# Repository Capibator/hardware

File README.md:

# V1.0 -> First tentative version with following features: 
made with Kicad, 2 layers, lots of vias :D 
- battery monitoring
- battery charge/discharge maintanance LIPO 
- buck boost regulator TPS 
- Source selector that can select between mcu_bat or +12V automatically
- An RTC that can keep time even without battery. helpful for critical memory and notifications. 
- An optional IO expander (PCF) providing 8 extra GPIO. can be left unpopulated. pcb should work fine. 
- MCU used is ESP32 with bluetooth and wifi hopefully both being utillized
- Heater and egg turner both AC, egg turner is the continous type and is the only type currently supported. 
- Main Voltage being used is +12V provided by jack, that will power fans, logic board. incase of power outage heavy stuff will be turned off automatically and it will go into power saving mode. 
- Outputs (All 12V)
    - Fan Exhaust 
    - Fan Continous 
    - Mist Maker 
    - LED lights 
    - Buzzer
    - Water Pump 
- Sensors/Inputs
    - Water level sensor
    - Display (I2C)
    - Rotary encoder for menu (left, right and click)
    - Temperature sensor (1 wire or digital)
    - Temperature sensor #2 (1 wire or digital)
- Indicators
    - Fault led, will light up if something is wrong according to code
    - Busy led, will turn on when turning eggs or saving to memory 
    - Con led, shows connectivity of wifi, if connected will light up
    - IO led, custom function or initial testing. 
    - Main power indicator led that will light up when 12V is connected through barrel jack. 

This is how it looks as of right now. 

PCB 

# Version 2 
Better placement, hopefully this is better. 
AC in one end and sensitive logic on the other. 

size 101.5mm x 61.4mm

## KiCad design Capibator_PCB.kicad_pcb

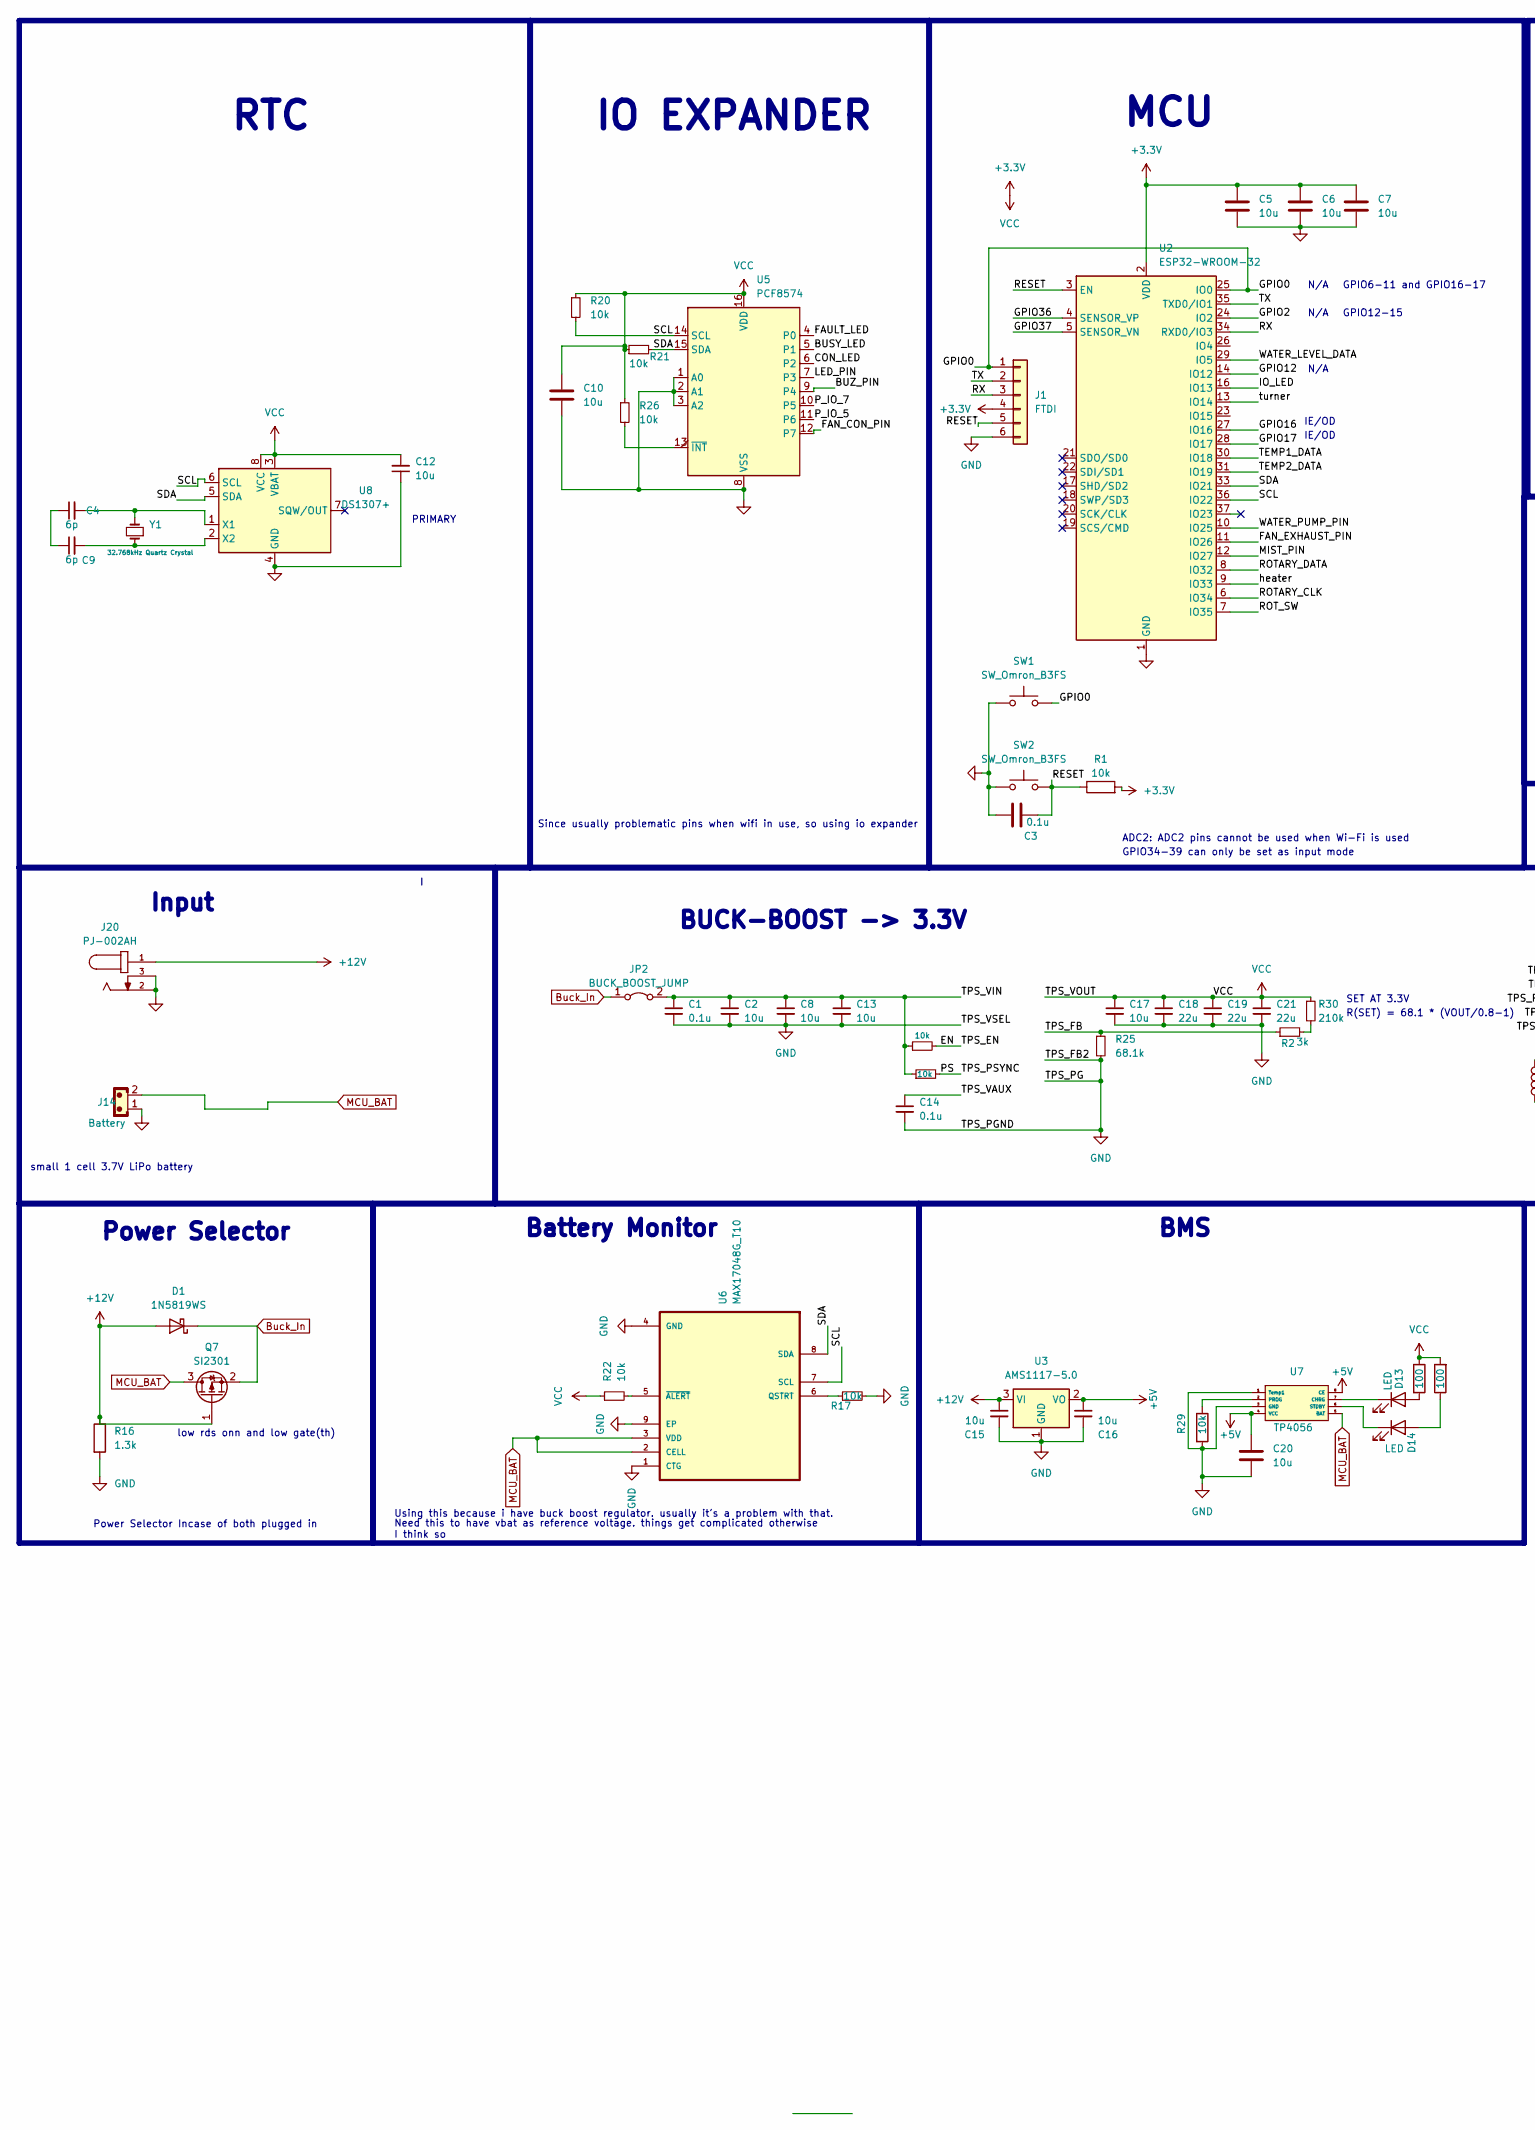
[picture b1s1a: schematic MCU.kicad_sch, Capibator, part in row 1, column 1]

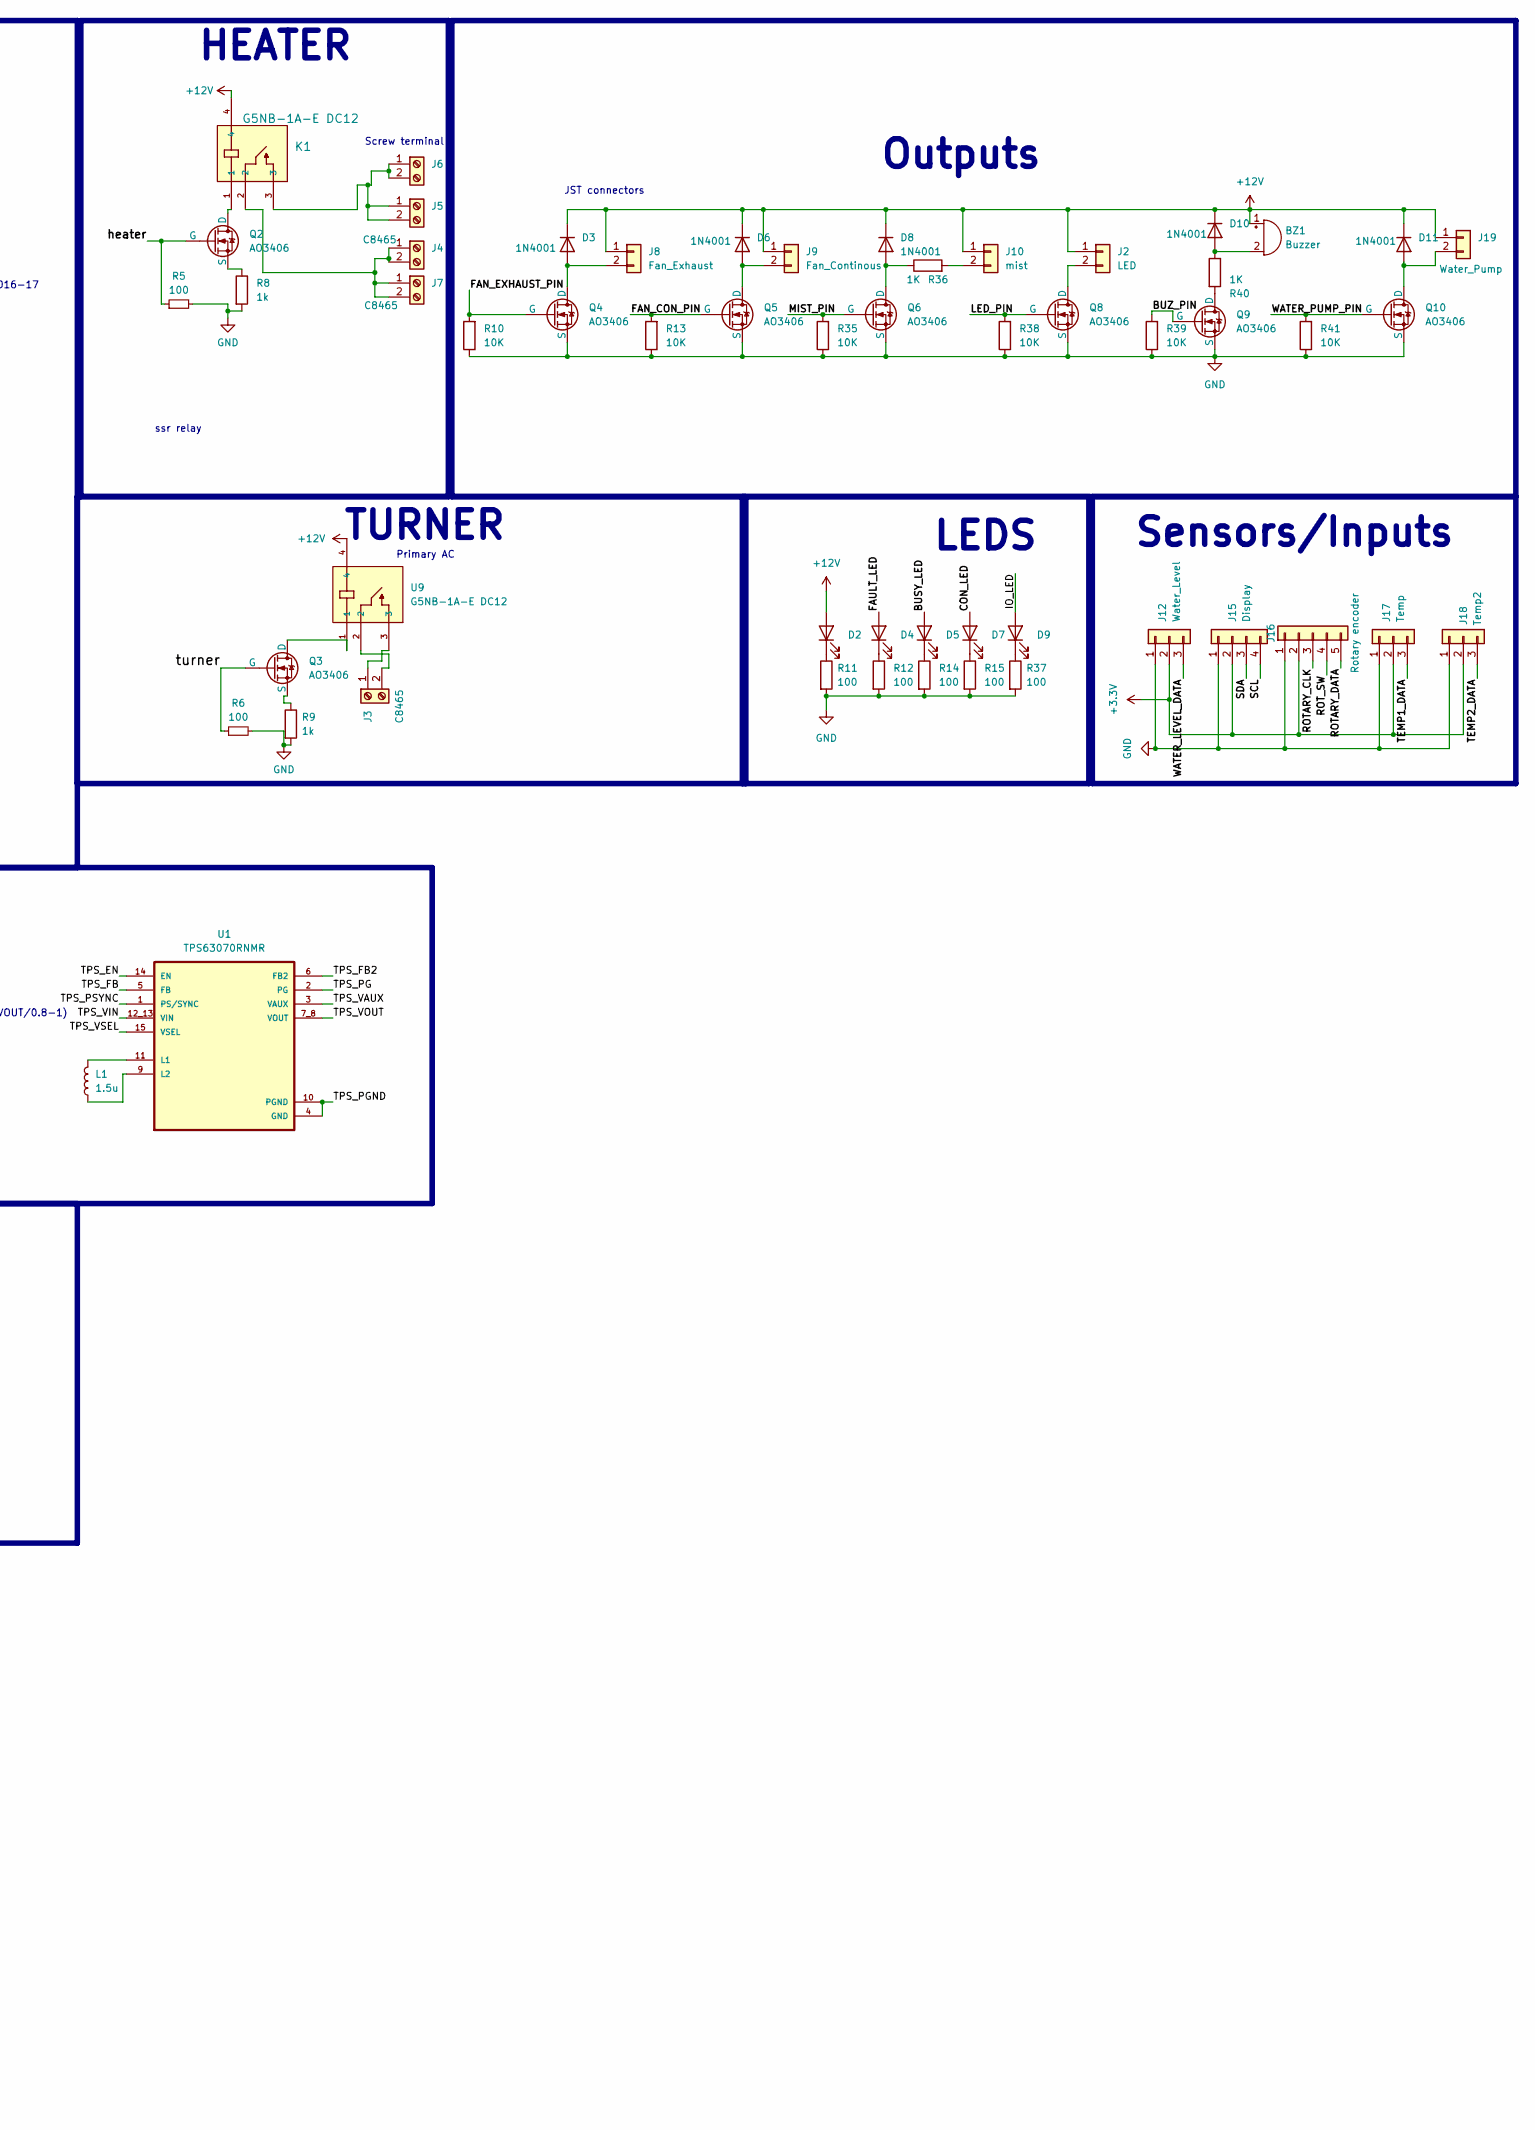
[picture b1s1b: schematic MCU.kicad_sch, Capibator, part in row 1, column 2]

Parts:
BZ1: Buzzer; Buzzer_12x9.5RM7.6
C1, C3, C14: 0.1u; C_0805_2012Metric
C2, C5, C6, C7, C8, C10, C12, C13, C15, C16, C20: 10u; C_0805_2012Metric
C4, C9: 6p; C_0805_2012Metric
C17: 10u; R_0805_2012Metric
C18, C19, C21: 22u; R_0805_2012Metric
D1: 1N5819WS; D_SOD-323F
D2: LED_PWR; LED_0805_2012Metric
D3, D6, D8, D10, D11: 1N4001; D_SOD-123F
D4: FAULT_LED; LED_0805_2012Metric
D5: BUSY_LED; D_0805_2012Metric
D7: CONNECTIVITY_LED; LED_0805_2012Metric
D9, D13, D14: LED; LED_0805_2012Metric
J1: FTDI; PinHeader_1x06_P2.54mm_Vertical
J2: LED; JST_GH_SM02B-GHS-TB_1x02-1MP_P1.25mm_Horizontal
J3, J4, J5, J6, J7: C8465; TerminalBlock_Altech_AK300-2_P5.00mm
J8: Fan_Exhaust; JST_GH_SM02B-GHS-TB_1x02-1MP_P1.25mm_Horizontal
J9: Fan_Continous; JST_GH_SM02B-GHS-TB_1x02-1MP_P1.25mm_Horizontal
J10: mist; JST_GH_SM02B-GHS-TB_1x02-1MP_P1.25mm_Horizontal
J12: Water_Level; JST_GH_SM03B-GHS-TB_1x03-1MP_P1.25mm_Horizontal
J14: Battery; JST_EH_B2B-EH-A_1x02_P2.50mm_Vertical
J15: Display; JST_GH_BM04B-GHS-TBT_1x04-1MP_P1.25mm_Vertical
J16: Rotary encoder; JST_GH_BM05B-GHS-TBT_1x05-1MP_P1.25mm_Vertical
J17: Temp; JST_GH_SM03B-GHS-TB_1x03-1MP_P1.25mm_Horizontal
J18: Temp2; JST_GH_SM03B-GHS-TB_1x03-1MP_P1.25mm_Horizontal
J19: Water_Pump; JST_GH_SM02B-GHS-TB_1x02-1MP_P1.25mm_Horizontal
J20: PJ-002AH; CUI_PJ-002AH
JP2: BUCK_BOOST_JUMP; SolderJumper-2_P1.3mm_Bridged_RoundedPad1.0x1.5mm
K1: G5NB-1A-E DC12; RELAY_G5NB-1A_DC5_OMR; MANUFACTURER_PART_NUMBER G5NB-1A-E DC12
L1: 1.5u; L_Murata_LQH2MCNxxxx02_2.0x1.6mm
Q2, Q3, Q4, Q5, Q6, Q8, Q9, Q10: AO3406; SOT-23
Q7: SI2301; SOT-23
R1, R17, R20, R21, R22, R23, R24, R26, R29: 10k; R_0805_2012Metric
R2: 3k; R_0805_2012Metric
R5, R6, R11, R12, R14, R15, R31, R32, R37: 100; R_0805_2012Metric
R8, R9: 1k; R_0805_2012Metric
R10, R13, R35, R38, R39, R41: 10K; R_0805_2012Metric
R16: 1.3k; R_0805_2012Metric
R25: 68.1k; R_0805_2012Metric
R30: 210k; R_0805_2012Metric
R36: 1K; D_SOD-123F
R40: 1K; R_0805_2012Metric
SW1, SW2: SW_Omron_B3FS; SW_SPST_Omron_B3FS-100xP
U1: TPS63070RNMR; VREG_TPS63070RNMR
U2: ESP32-WROOM-32
U3: AMS1117-5.0; SOT-223-3_TabPin2
U5: PCF8574; SOIC127P1032X265-16N
U6: MAX17048G_T10; SON50P200X200X80-9N
U7: TP4056; SOP127P600X175-9N
U8: DS1307+; 21-0041B_8
U9: G5NB-1A-E DC12; RELAY_G5NB-1A_DC5_OMR; MANUFACTURER_PART_NUMBER G5NB-1A-E DC12
Y1: 32.768kHz Quartz Crystal; Crystal_SMD_2012-2Pin_2.0x1.2mm_HandSoldering

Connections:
12V_status: U2.23 (IO15)
+3.3V: C5.2, C6.1, C7.1, C10.2, C12.2, C17.1, C18.1, C19.1, C21.1, J1.4, J12.2, J15.2, J16.2, J17.2, J18.2, R1.2, R20.1, R21.1, R22.1, R26.1, R30.1, R31.1, R32.2, U1.7_8 (VOUT), U2.2 (VDD), U5.16 (VDD), U8.3 (VBAT), U8.8 (VCC); also elsewhere on the board
+5V: C16.1, C20.1, U3.2 (VO), U7.4 (VCC), U7.8 (CE)
+12V: BZ1.1 (-), C15.1, D1.2 (A), D2.2 (A), D3.1 (K), D6.1 (K), D8.1 (K), D10.1 (K), D11.1 (K), J2.1, J8.1, J9.1, J10.1, J19.1, J20.1, K1.4, Q7.1 (G), R16.1, U3.3 (VI), U9.4
/MCU/BUSY_LED: D5.2 (A), U5.5 (P1)
/MCU/BUZ_PIN: Q9.2 (G), R39.2, U5.9 (P4)
/MCU/CON_LED: D7.2 (A), U5.6 (P2)
/MCU/EN: R23.2, U1.14 (EN)
/MCU/FAN_CON_PIN: Q5.2 (G), R13.2, U5.12 (P7)
/MCU/FAN_EXHAUST_PIN: Q4.2 (G), R10.2, U2.11 (IO26)
/MCU/FAULT_LED: D4.2 (A), U5.4 (P0)
/MCU/GPIO0: J1.1, SW1.2, U2.25 (IO0)
/MCU/GPIO2: U2.24 (IO2)
/MCU/GPIO12: U2.14 (IO12)
/MCU/GPIO16: U2.27 (IO16)
/MCU/GPIO17: U2.28 (IO17)
/MCU/GPIO36: U2.4 (SENSOR_VP)
/MCU/GPIO37: U2.5 (SENSOR_VN)
/MCU/IO_LED: D9.2 (A), U2.16 (IO13)
/MCU/LED_PIN: Q8.2 (G), R38.2, U5.7 (P3)
/MCU/MIST_PIN: Q6.2 (G), R35.2, U2.12 (IO27)
/MCU/PS: R24.2, U1.1 (PS/SYNC)
/MCU/P_IO_5: U5.11 (P6)
/MCU/P_IO_7: U5.10 (P5)
/MCU/RESET: C3.2, J1.5, R1.1, SW2.2, U2.3 (EN)
/MCU/ROTARY_CLK: J16.3, U2.6 (IO34)
/MCU/ROTARY_DATA: J16.5, U2.8 (IO32)
/MCU/ROT_SW: J16.4, U2.7 (IO35)
/MCU/RX: J1.3, U2.34 (RXD0/IO3)
/MCU/SCL: J15.4, R20.2, U2.36 (IO22), U5.14 (SCL), U6.7 (SCL), U8.6 (SCL); also elsewhere on the board
/MCU/SDA: J15.3, R21.2, U2.33 (IO21), U5.15 (SDA), U6.8 (SDA), U8.5 (SDA)
/MCU/TEMP1_DATA: J17.3, U2.30 (IO18)
/MCU/TEMP2_DATA: J18.3, U2.31 (IO19)
/MCU/TPS_FB: R2.1, R25.1, U1.5 (FB)
/MCU/TPS_VAUX: C14.1, U1.3 (VAUX)
/MCU/TPS_VIN: C1.1, C2.1, C8.1, C13.1, JP2.2 (B), R23.1, R24.1, U1.12_13 (VIN)
/MCU/TX: J1.2, U2.35 (TXD0/IO1)
/MCU/WATER_LEVEL_DATA: J12.3, U2.29 (IO5)
/MCU/WATER_PUMP_PIN: Q10.2 (G), R41.2, U2.10 (IO25)
/MCU/heater: Q2.2 (G), R5.1, U2.9 (IO33)
/MCU/turner: Q3.2 (G), R6.1, U2.13 (IO14)
Buck_In: D1.1 (K), JP2.1 (A), Q7.2 (S)
GND: C1.2, C2.2, C3.1, C5.1, C6.2, C7.2, C8.2, C10.1, C12.1, C13.2, C14.2, C15.2, C16.2, C17.2, C18.2, C19.2, C20.2, C21.2, J1.6, J12.1, J14.1, J15.1, J16.1, J17.1, J18.1, J20.2, J20.3, Q4.3 (S), Q5.3 (S), Q6.3 (S), Q8.3 (S), Q9.3 (S), Q10.3 (S), R5.2, R6.2, R8.2, R9.2, R10.1, R11.2, R12.2, R13.1, R14.2, R15.2, R16.2, R17.2, R25.2, R29.2, R35.1, R37.2, R38.1, R39.1, R41.1, SW1.1, SW2.1, U1.2 (PG), U1.4 (GND), U1.6 (FB2), U1.10 (PGND), U1.15 (VSEL), U2.1 (GND), U2.15 (GND), U2.38 (GND), U2.39 (GND), U3.1 (GND), U5.1 (A0), U5.2 (A1), U5.3 (A2), U5.8 (VSS), U6.1 (CTG), U6.4 (GND), U6.9 (EP), U7.1 (Temp1), U7.3 (GND), U8.4 (GND)
MCU_BAT: J14.2, Q7.3 (D), U6.2 (CELL), U6.3 (VDD), U7.5 (BAT)
unnamed: BZ1.2 (+), D10.2 (A), R40.1
unnamed: C4.1, C9.1
unnamed: D2.1 (K), R11.1
unnamed: D3.2 (A), J8.2, Q4.1 (D)
unnamed: D4.1 (K), R12.1
unnamed: D5.1 (K), R14.1
unnamed: D6.2 (A), J9.2, Q5.1 (D)
unnamed: D7.1 (K), R15.1
unnamed: D8.2 (A), Q6.1 (D), R36.1
unnamed: D9.1 (K), R37.1
unnamed: D11.2 (A), J19.2, Q10.1 (D)
unnamed: D13.2 (A), R31.2
unnamed: D13.1 (K), U7.7 (CHRG)
unnamed: D14.2 (A), R32.1
unnamed: D14.1 (K), U7.6 (STDBY)
unnamed: J2.2, Q8.1 (D)
unnamed: J3.1, U9.3
unnamed: J3.2, U9.2
unnamed: J4.1, J4.2, J7.1, J7.2, K1.2
unnamed: J5.1, J5.2, J6.1, J6.2, K1.3
unnamed: J10.2, R36.2
unnamed: K1.1, Q2.1 (D)
unnamed: Q2.3 (S), R8.1
unnamed: Q3.1 (D), U9.1
unnamed: Q3.3 (S), R9.1
unnamed: Q9.1 (D), R40.2
unnamed: R2.2, R30.2
unnamed: L1.2, U1.11 (L1)
unnamed: L1.1, U1.9 (L2)
unnamed: R26.2, U5.13 (~INT)
unnamed: R17.1, U6.6 (QSTRT)
unnamed: R22.2, U6.5 (~ALERT)
unnamed: R29.1, U7.2 (PROG)
unnamed: C4.2, U8.1 (X1), Y1.2
unnamed: C9.2, U8.2 (X2), Y1.1

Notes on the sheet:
Battery Monitor
RTC
LEDS
Using this because i have buck boost regulator. usually it's a problem with that.
low rds onn and low gate(th)
MCU
GPIO34-39 can only be set as input mode
ssr relay
PRIMARY
BMS
GPIO6-11 and GPIO16-17
IE/OD
N/A
Screw terminal
R(SET) = 68.1 * (VOUT/0.8-1)
ADC2: ADC2 pins cannot be used when Wi-Fi is used
IO EXPANDER
Outputs
HEATER
SET AT 3.3V
TURNER
small 1 cell 3.7V LiPo battery
Need this to have vbat as reference voltage. things get complicated otherwise I think so
BUCK-BOOST -> 3.3V
JST connectors
Power Selector Incase of both plugged in
Sensors/Inputs
Since usually problematic pins when wifi in use, so using io expander
Primary AC
GPIO12-15
Input
Power Selector

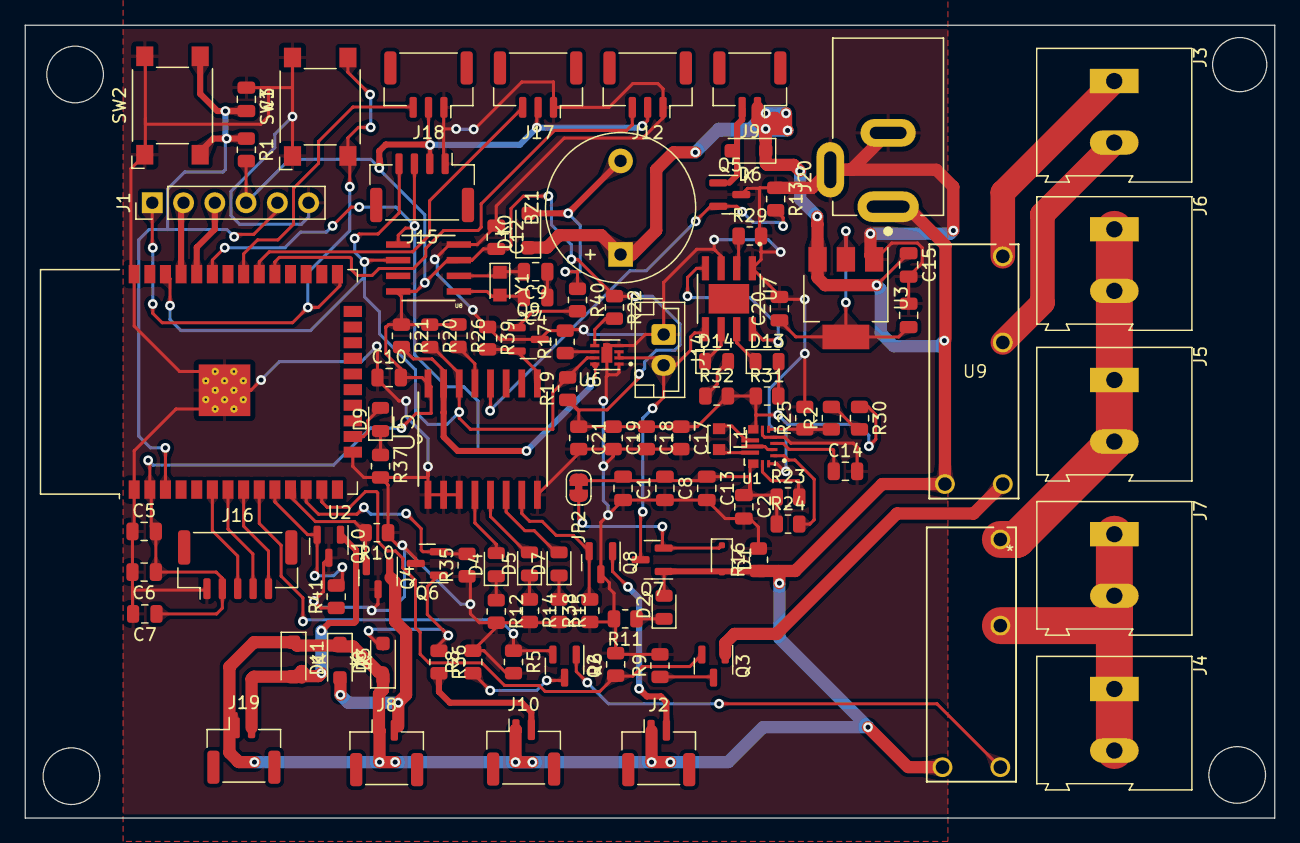
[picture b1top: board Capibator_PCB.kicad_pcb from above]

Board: 2 copper layers, 101.5 x 64.4 mm, 108 parts (0 on the bottom side), 70 nets.

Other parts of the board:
R19: 10k; R_0805_2012Metric

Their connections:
+3.3V: R19.1; also elsewhere on the board
/MCU/SCL: R19.2; also elsewhere on the board

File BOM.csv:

"Reference","Value","Datasheet","Footprint","Qty","DNP"
"BZ1","Buzzer","~","Buzzer_Beeper:Buzzer_12x9.5RM7.6","1",""
"C1,C3,C14","0.1u","~","Capacitor_SMD:C_0805_2012Metric","3",""
"C2,C5,C6,C7,C8,C10,C13,C15,C16,C17,C20","10u","~","-- mixed values --","11",""
"C4,C9","6p","~","Capacitor_SMD:C_0805_2012Metric","2",""
"C12","C_Small","~","Capacitor_SMD:C_0805_2012Metric","1",""
"C18,C19,C21","22u","~","Resistor_SMD:R_0805_2012Metric","3",""
"D1","1N5819WS","https://datasheet.lcsc.com/lcsc/2204281430_Guangdong-Hottech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","Diode_SMD:D_0805_2012Metric","1",""
"D2","LED_PWR","~","LED_SMD:LED_0805_2012Metric","1",""
"D3,D6,D8,D10,D11","1N4001","http://www.vishay.com/docs/88503/1n4001.pdf","Diode_SMD:D_0805_2012Metric","5",""
"D4","FAULT_LED","~","LED_SMD:LED_0805_2012Metric","1",""
"D5","BUSY_LED","~","Diode_SMD:D_0805_2012Metric","1",""
"D7","CONNECTIVITY_LED","~","LED_SMD:LED_0805_2012Metric","1",""
"D9,D13,D14,J2","LED","~","-- mixed values --","4",""
"F1","CAR_FUSE 2A","~","Fuse:Fuse_1206_3216Metric","1",""
"J1","FTDI","~","Connector_PinHeader_2.54mm:PinHeader_1x06_P2.54mm_Vertical","1",""
"J3,J4,J6","C8465","~","TerminalBlock:TerminalBlock_Altech_AK300-2_P5.00mm","3",""
"J5","PJ-002AH","","PJ-002AH:CUI_PJ-002AH","1",""
"J8","Fan_Exhaust","~","Connector_JST:JST_GH_SM02B-GHS-TB_1x02-1MP_P1.25mm_Horizontal","1",""
"J9","Fan_Continous","~","Connector_JST:JST_GH_SM02B-GHS-TB_1x02-1MP_P1.25mm_Horizontal","1",""
"J10","mist","~","Connector_JST:JST_GH_SM02B-GHS-TB_1x02-1MP_P1.25mm_Horizontal","1",""
"J12","Water_Level","~","Connector_JST:JST_GH_SM03B-GHS-TB_1x03-1MP_P1.25mm_Horizontal","1",""
"J14","Battery","","Connector_JST:JST_EH_B2B-EH-A_1x02_P2.50mm_Vertical","1",""
"J15","Display","~","Connector_JST:JST_GH_BM04B-GHS-TBT_1x04-1MP_P1.25mm_Vertical","1",""
"J16","Rotary encoder","~","Connector_JST:JST_GH_BM05B-GHS-TBT_1x05-1MP_P1.25mm_Vertical","1",""
"J17","Temp","~","Connector_JST:JST_GH_SM03B-GHS-TB_1x03-1MP_P1.25mm_Horizontal","1",""
"J18","Temp2","~","Connector_JST:JST_GH_SM03B-GHS-TB_1x03-1MP_P1.25mm_Horizontal","1",""
"J19","Water_Pump","~","Connector_JST:JST_GH_SM02B-GHS-TB_1x02-1MP_P1.25mm_Horizontal","1",""
"JP2","BUCK_BOOST_JUMP","~","Jumper:SolderJumper-2_P1.3mm_Bridged_RoundedPad1.0x1.5mm","1",""
"K1,U9","G5NB-1A-E DC12","-- mixed values --","G5NB-1A-E_DC12:RELAY_G5NB-1A_DC5_OMR","2",""
"L1","1.5u","~","Inductor_SMD:L_0805_2012Metric","1",""
"Q2,Q3,Q4,Q5,Q6,Q8,Q9,Q10","AO3406","https://ngspice.sourceforge.io/docs/ngspice-manual.pdf","Package_TO_SOT_SMD:SOT-23","8",""
"Q7","SI2301","http://www.vishay.com/docs/66709/si2319cd.pdf","Package_TO_SOT_SMD:SOT-23","1",""
"R1,R17,R20,R21,R22,R23,R24,R26,R29","10k","~","Resistor_SMD:R_0805_2012Metric","9",""
"R5,R6","330","~","Resistor_SMD:R_0805_2012Metric","2",""
"R8,R9","1k","~","Resistor_SMD:R_0805_2012Metric","2",""
"R10,R13,R35,R38,R39,R41","10K","~","Resistor_SMD:R_0805_2012Metric","6",""
"R11,R12,R14,R15,R36,R37,R40","1K","~","Resistor_SMD:R_0805_2012Metric","7",""
"R16","1.3k","~","Resistor_SMD:R_0805_2012Metric","1",""
"R25","68.1k","~","Resistor_SMD:R_0805_2012Metric","1",""
"R30","213k","~","Resistor_SMD:R_0805_2012Metric","1",""
"R31,R32","1.5k","~","Resistor_SMD:R_0805_2012Metric","2",""
"SW1,SW2","SW_Omron_B3FS","https://omronfs.omron.com/en_US/ecb/products/pdf/en-b3fs.pdf","Button_Switch_SMD:SW_SPST_Omron_B3FS-100xP","2",""
"U1","TPS63070RNMR","","TPS63070RNMR:VREG_TPS63070RNMR","1",""
"U2","ESP32-WROOM-32","https://www.espressif.com/sites/default/files/documentation/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","RF_Module:ESP32-WROOM-32","1",""
"U3","AMS1117-5.0","http://www.advanced-monolithic.com/pdf/ds1117.pdf","Package_TO_SOT_SMD:SOT-223-3_TabPin2","1",""
"U5","PCF8574","http://www.nxp.com/docs/en/data-sheet/PCF8574_PCF8574A.pdf","PCF8574T_3_518:SOIC127P1032X265-16N","1",""
"U6","MAX17048G_T10","","MAX17048G_T10:SON50P200X200X80-9N","1",""
"U7","TP4056","","TP4056:SOP127P600X175-9N","1",""
"U8","DS1307+","https://datasheets.maximintegrated.com/en/ds/DS1307.pdf","DS1307ZTR:21-0041B_8","1",""
"Y1","32.768kHz Quartz Crystal","~","Crystal:Crystal_SMD_3215-2Pin_3.2x1.5mm","1",""

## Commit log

2024-01-21 mcu + in/out
2024-01-23 Power Section done + added backup lipo
2024-01-23 fixed R values
2024-01-24 added io expander + rtc + fuel guage
2024-02-05 Schematic Completed
2024-02-05 cleaned up file system
2024-03-13 assigned footprints. another look needed. moving to pcb
2024-03-14 started pcb and basic alignment
2024-03-26 started pcb
2024-06-16 improved schematic
2024-06-21 first revision of pcb ready. very crude.. needs another looky
2024-06-21 added readme version 1 update
2024-06-21 add models for better visuals
2024-06-22 started version 2, better placements without routing
2024-06-22 added picture to readme
2024-06-22 changed picture in readme
2024-06-22 generated bom for jlcpcb
2024-06-22 almost done
2024-06-22 corrected few mistakes, generated correct bom with lcsc part numbers
2024-06-23 cleaned up tracks, added teardrops, copper fill and improved spacing

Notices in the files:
parts and their libraries:
COPYRIGHT: Copyright (C) 2023 Ultra Librarian. All rights reserved.
